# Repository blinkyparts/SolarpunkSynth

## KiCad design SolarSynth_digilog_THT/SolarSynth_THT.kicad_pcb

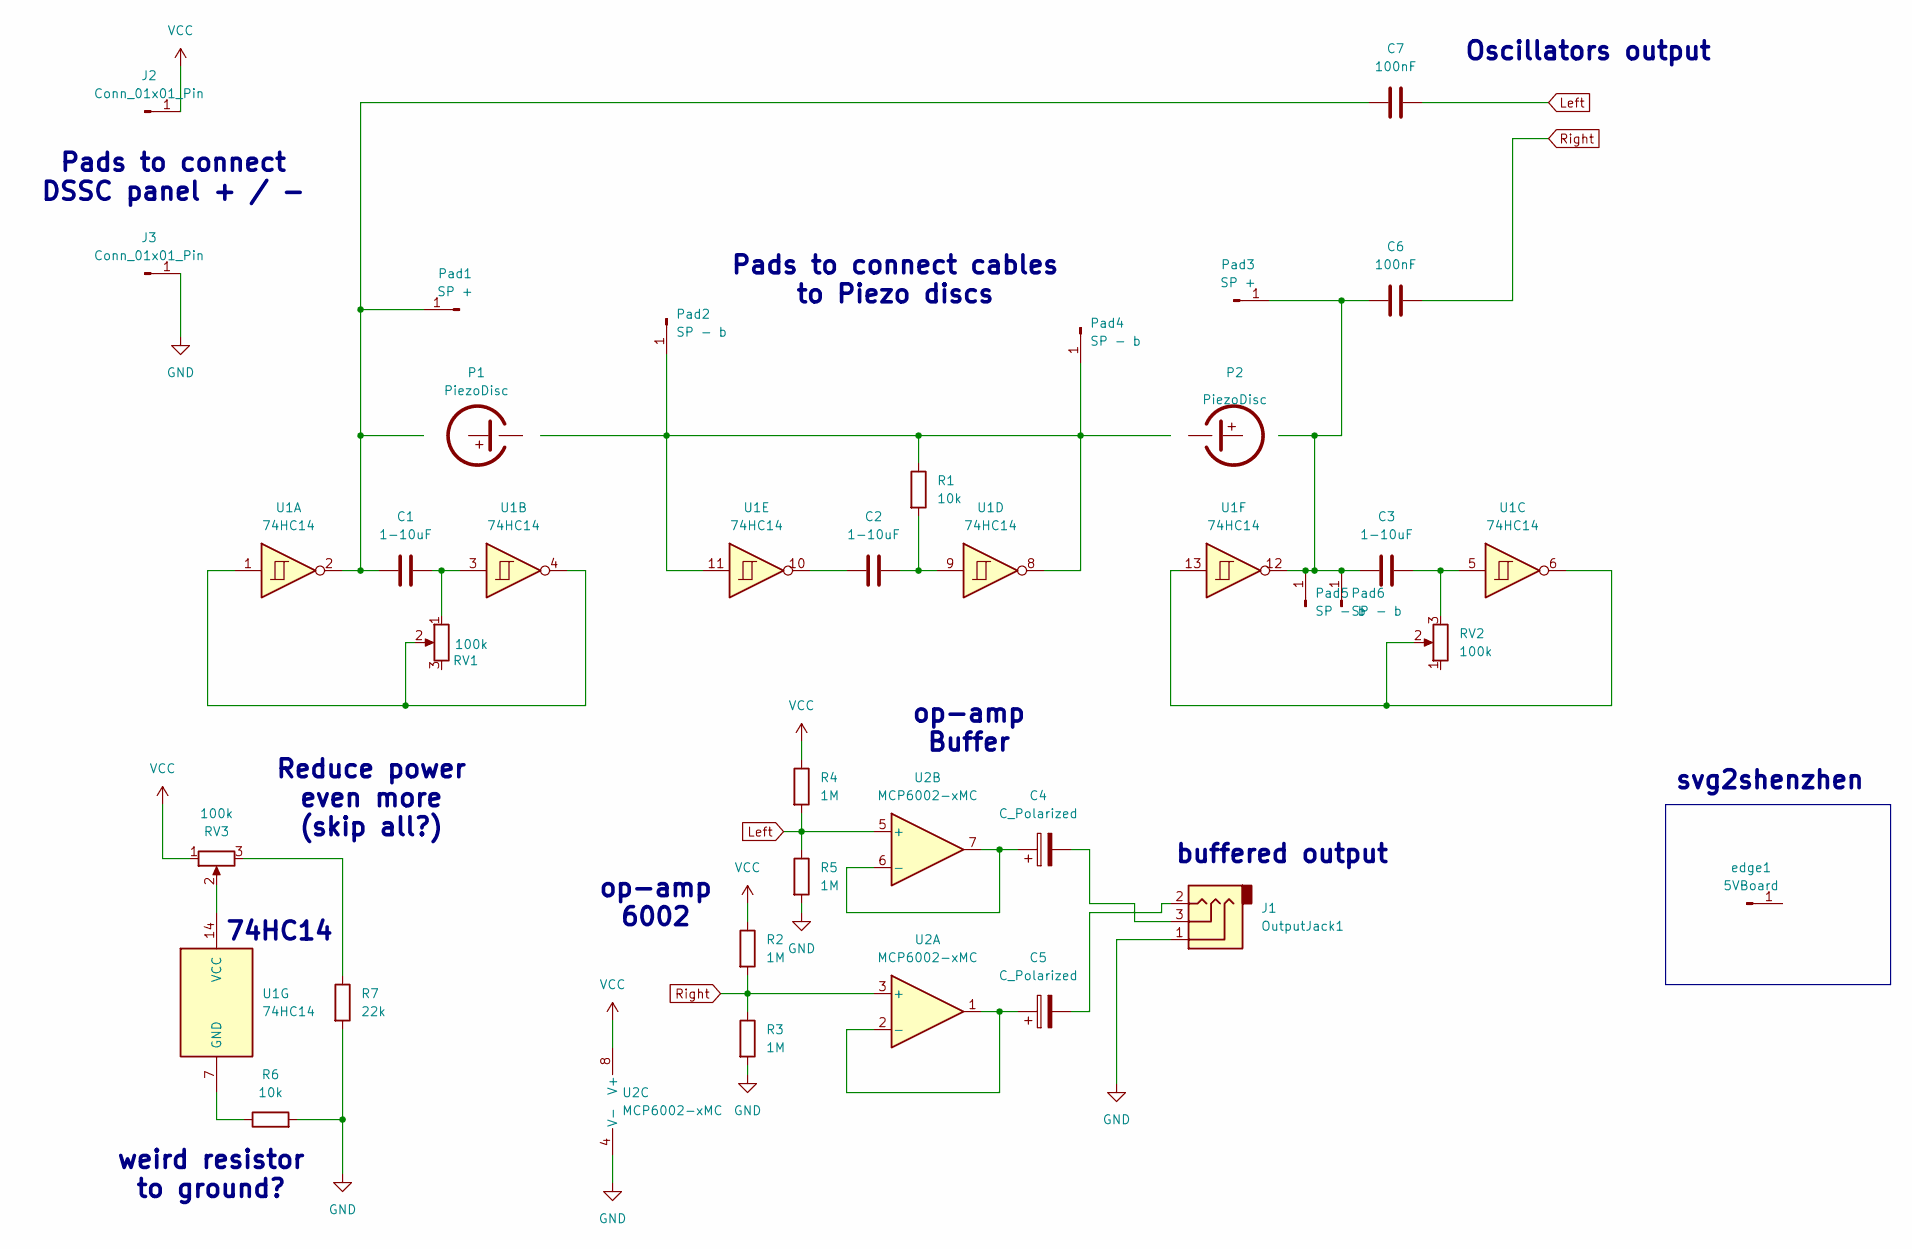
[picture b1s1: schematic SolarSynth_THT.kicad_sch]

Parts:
C1, C2, C3: 1-10uF; C_Disc_D5.0mm_W2.5mm_P5.00mm_handsoldering
C4, C5: C_Polarized; CP_Radial_D5.0mm_P2.50mm
C6, C7: 100nF; C_Disc_D5.0mm_W2.5mm_P2.50mm
J1: OutputJack1; AUDIO-JACK-3.5mm_SMD_noHole
J2, J3: Conn_01x01_Pin; SolarPad_VCC
P1, P2: PiezoDisc; Piezo_20mm
Pad1, Pad3: SP +; SolderPad_small
Pad2, Pad4, Pad5, Pad6: SP - b; SolderPad_small
R1, R6: 10k; R_Axial_DIN0309_L9.0mm_D3.2mm_P12.70mm_Horizontal
R2, R3, R4, R5: 1M; R_Axial_DIN0309_L9.0mm_D3.2mm_P12.70mm_Horizontal
R7: 22k; R_Axial_DIN0309_L9.0mm_D3.2mm_P12.70mm_Horizontal
RV1, RV2, RV3: 100k; Potentiometer_Alpha_RD901F-40-00D_Single_Vertical_bigger-ho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
U1: 74HC14; DIP-14_W7.62mm_LongerPads
U2: MCP6002-xMC; DIP-8_W7.62mm_LongPads
edge1: 5VBoard; board_digilog

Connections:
GND: J1.1, J3.1, R3.2, R5.2, R6.2, R7.2, U2.4 (V-), U2.9 (V-)
Left: C7.2, R4.2, R5.1, U2.5 (+)
unnamed: C1.2, RV1.1, U1.3
unnamed: C2.1, U1.10
unnamed: C2.2, R1.2, U1.9
unnamed: C3.2, RV2.3, U1.5
unnamed: C4.2, J1.3
unnamed: C5.2, J1.2
unnamed: C1.1, C7.1, Pad1.1, U1.2
unnamed: Pad2.1, Pad4.1, R1.1, U1.8, U1.11
unnamed: C3.1, C6.1, Pad3.1, Pad5.1, Pad6.1, U1.12
unnamed: R7.1, RV3.3
unnamed: RV1.2, U1.1, U1.4
unnamed: RV2.2, U1.6, U1.13
unnamed: R6.1, U1.7 (GND)
unnamed: RV3.2, U1.14 (VCC)
unnamed: C5.1, U2.1, U2.2 (-)
unnamed: C4.1, U2.6 (-), U2.7
Right: C6.2, R2.2, R3.1, U2.3 (+)
VCC: J2.1, R2.1, R4.1, RV3.1, U2.8 (V+)

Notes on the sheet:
svg2shenzhen
Pads to connect cables to Piezo discs
Oscillators output
Reduce power even more (skip all?)
op-amp Buffer
op-amp 6002
weird resistor to ground?
74HC14
buffered output
Pads to connect DSSC panel + / -

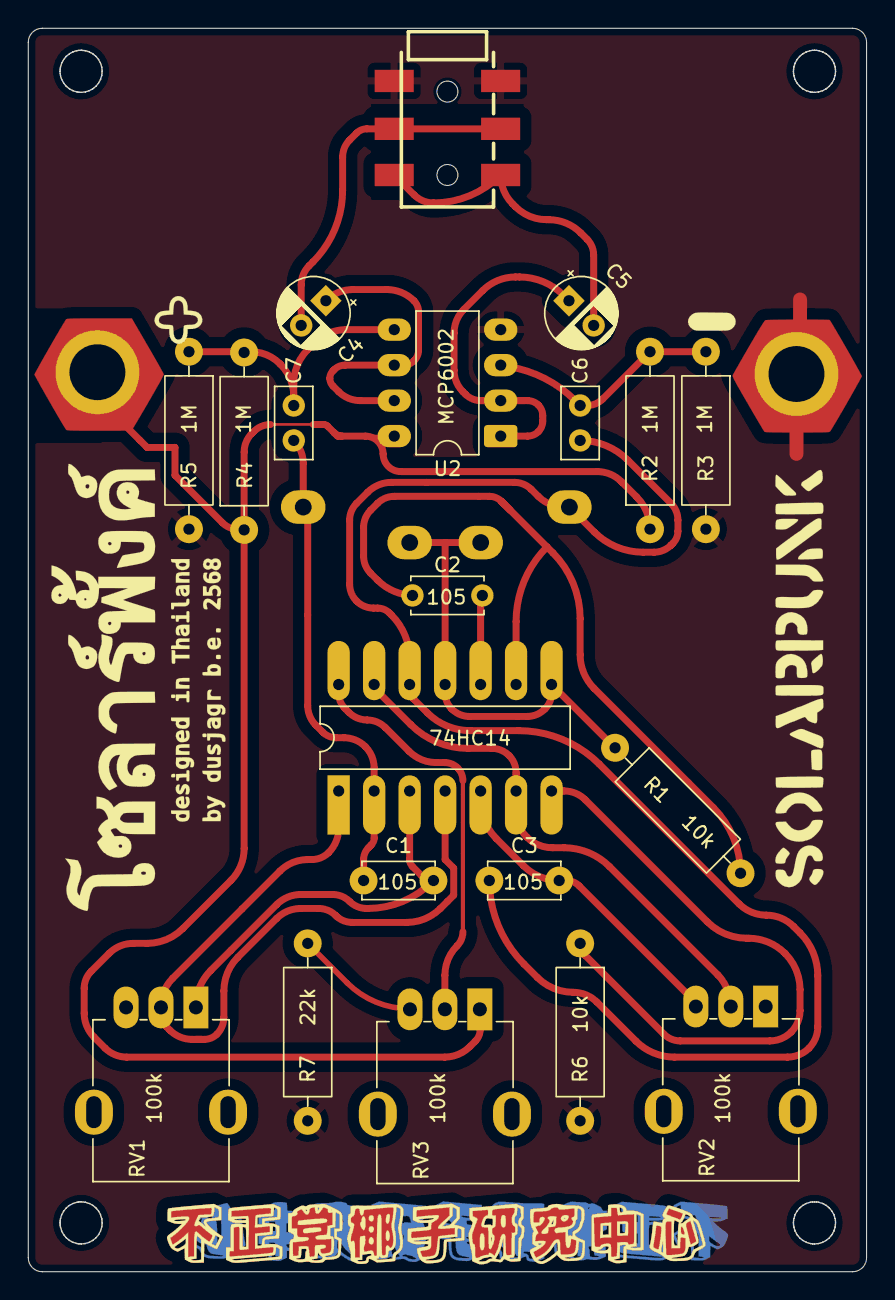
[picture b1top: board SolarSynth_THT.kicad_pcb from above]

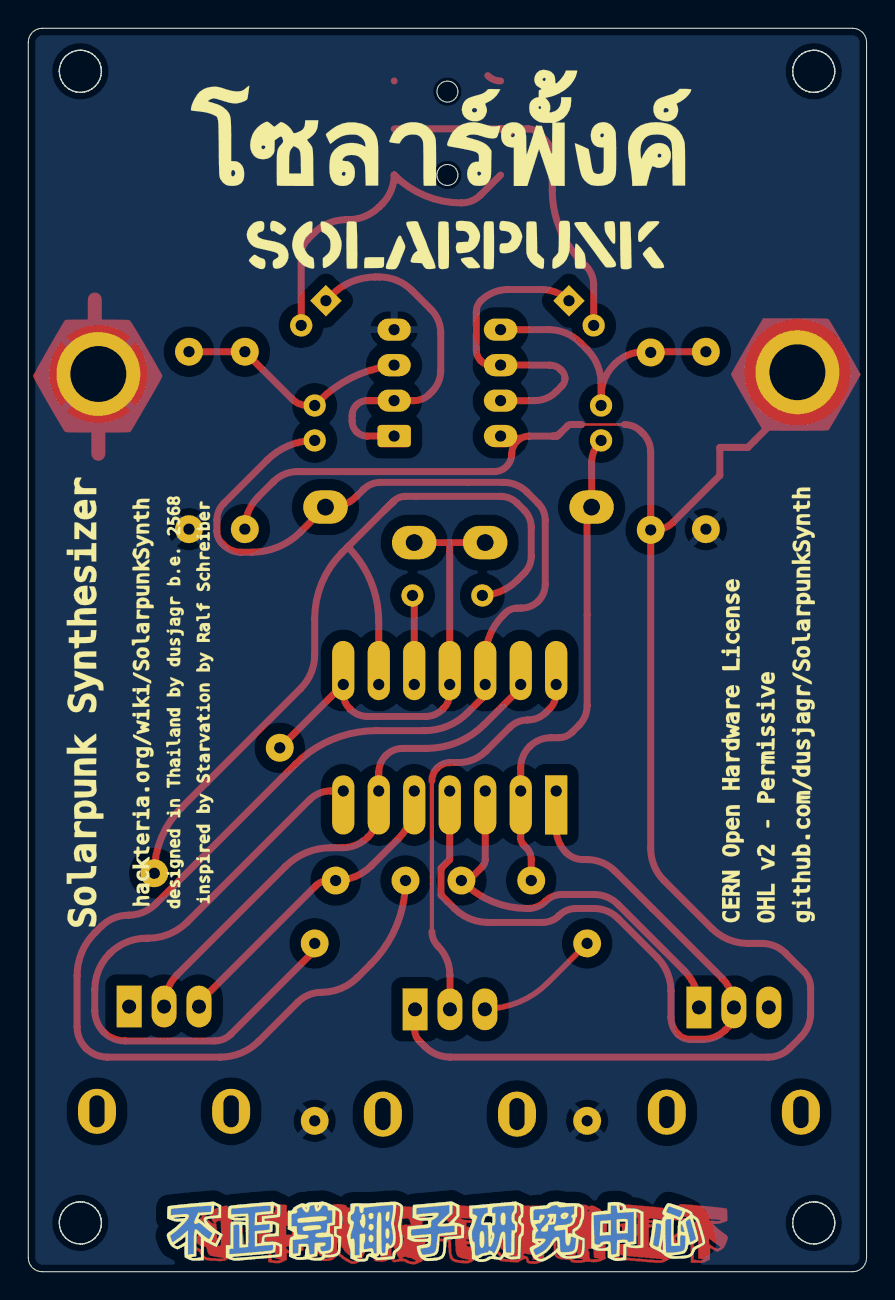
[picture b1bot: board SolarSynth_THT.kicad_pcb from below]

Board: 2 copper layers, 60.0 x 89.0 mm, 33 parts (3 on the bottom side), 20 nets.

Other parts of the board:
Ref**: Val**; graphix_digilog
Ref**#2: Val**; back_graphix_digilog
blinkyparts_logo_15mm: G***; logo_15mm
ce-symbol_mask_3mm: G***; ce-icon_3mm
weee-symbol_mask_3mm: G***; weee-icon_3mm

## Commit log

2025-03-05 poti-footprint changed
2025-03-05 Change SMD to THT
2025-03-05 gerber-files created
2025-03-19 fixed some bugs
2025-04-09 added original digilog again and moved THT-Version to a new folder
2026-01-10 fixed some errors. Made it easier to solder and added blinkyparts logo
